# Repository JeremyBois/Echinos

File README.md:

# Echinos
Evolution of Ptechinos keyboard

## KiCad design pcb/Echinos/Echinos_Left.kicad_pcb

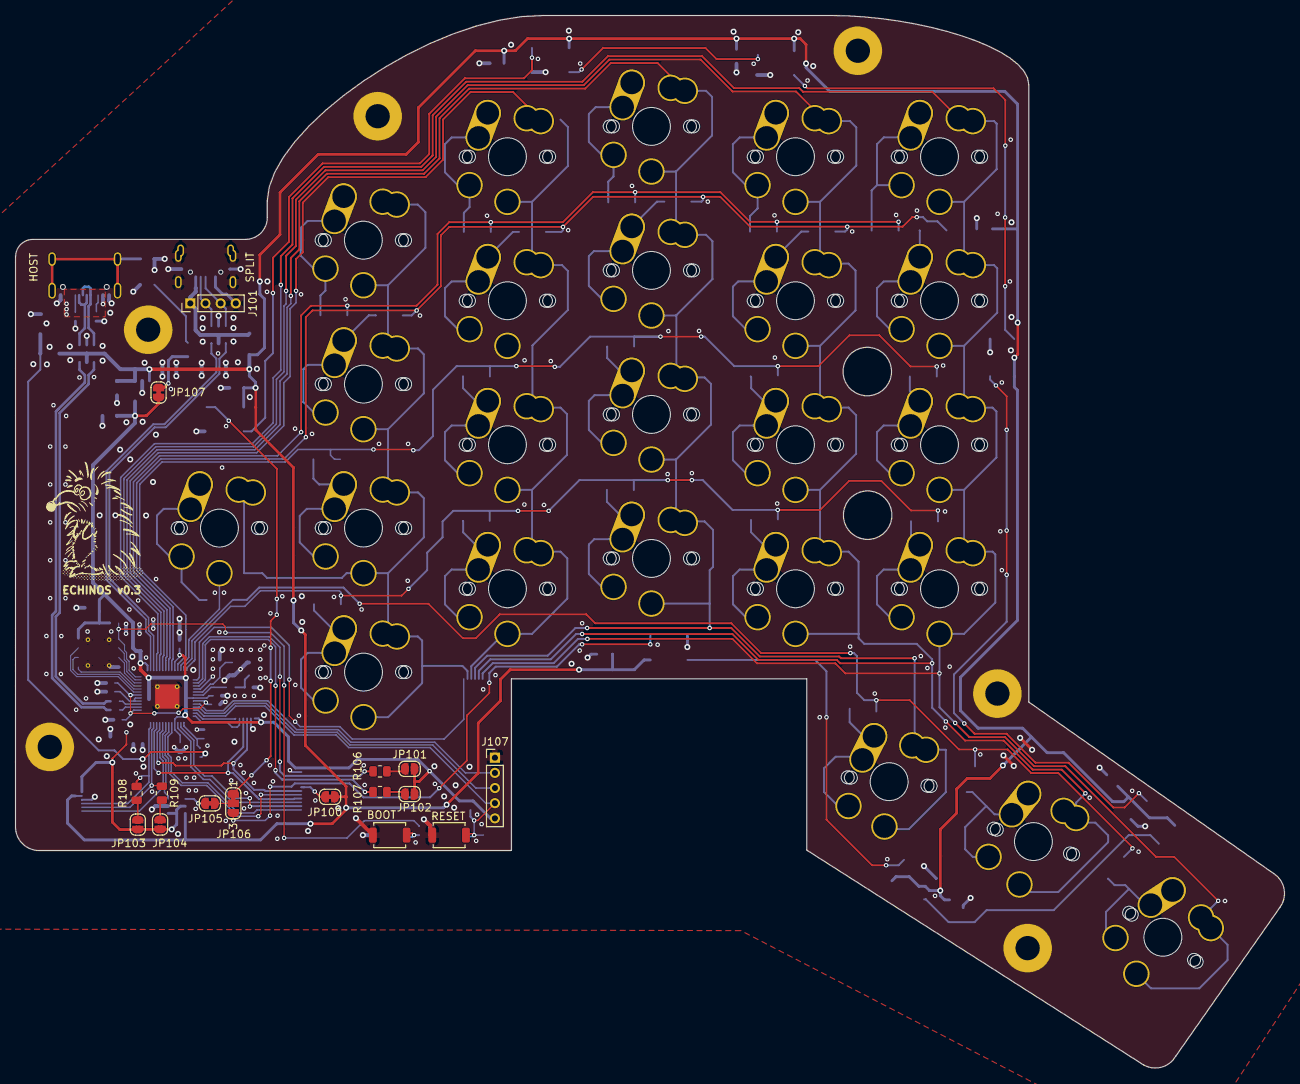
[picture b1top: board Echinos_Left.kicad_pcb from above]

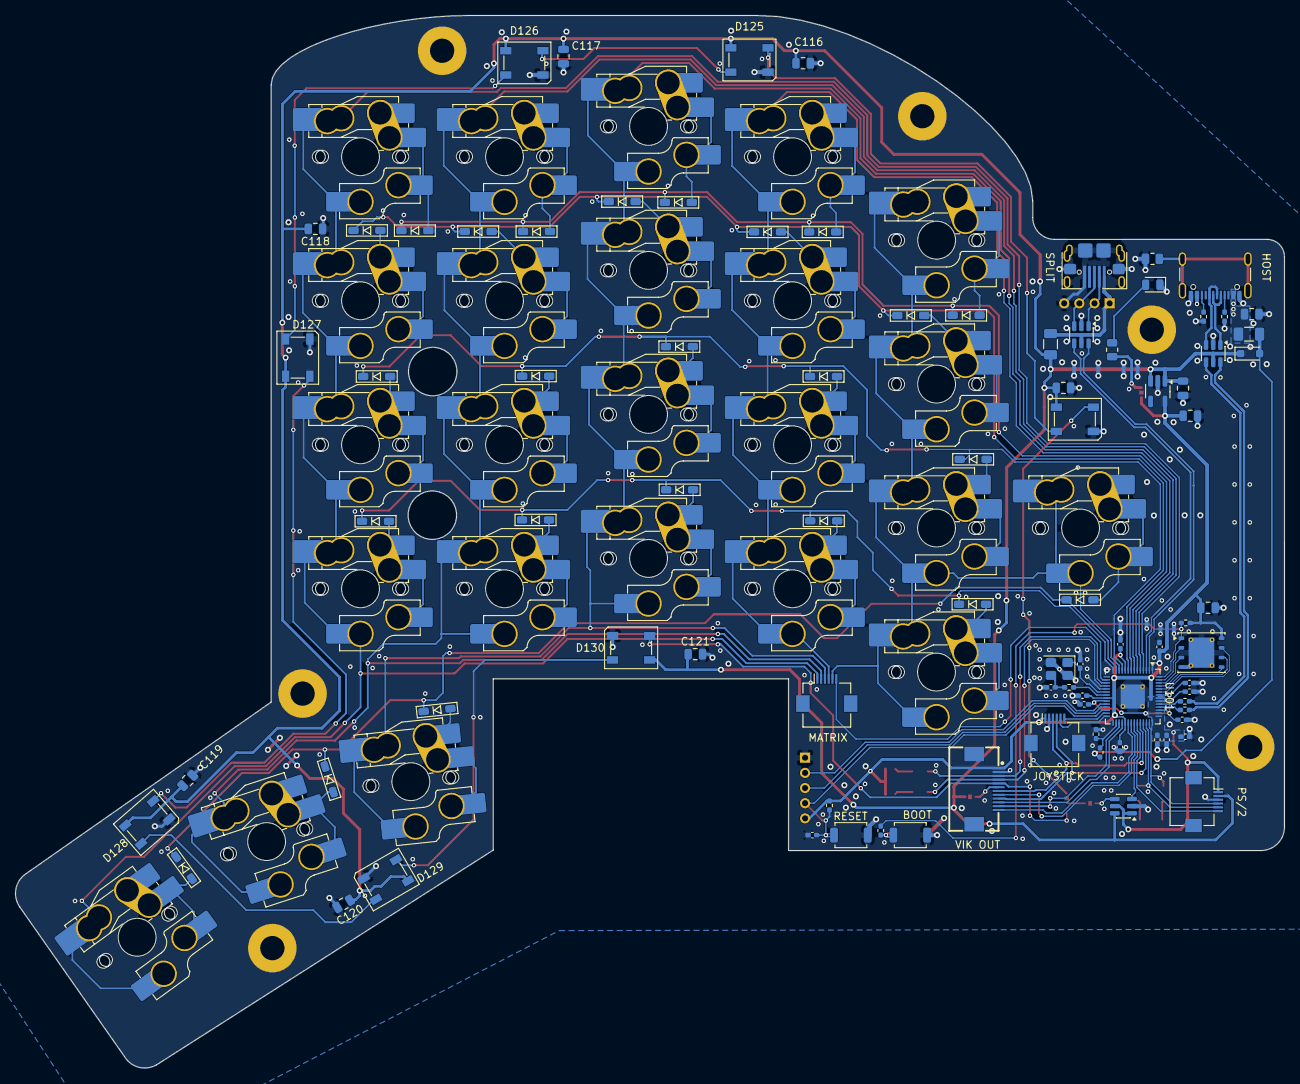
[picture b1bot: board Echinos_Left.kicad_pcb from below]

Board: 2 copper layers, 167.4 x 138.9 mm, 134 parts (87 on the bottom side), 100 nets.

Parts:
A1: Echinos Logo; Graphics_Hedgehog
C100, C106, C110: 1u; C_0402_1005Metric_Pad0.74x0.62mm_HandSolder
C101, C115, C116, C117, C118, C119, C120, C121: 100n; C_0805_2012Metric
C102, C103: 15p; C_0402_1005Metric_Pad0.74x0.62mm_HandSolder
C104, C105, C107, C108, C109, C111, C112, C113, C114: 100n; C_0402_1005Metric_Pad0.74x0.62mm_HandSolder
C122: 10u; C_0805_2012Metric
C123, C124: 1u; C_0805_2012Metric
D100, D101, D102, D103, D104, D105, D106, D107, D108, D109, D110, D111, D112, D113, D114, D115, D116, D117, D118, D119, D120, D121, D122, D123: D; D_SOD123
D124, D125, D126, D127, D128, D129, D130: SK6812; LED_SK6812_PLCC4_5.0x5.0mm_P3.2mm
D131: B5817WS; D_SOD-323_HandSoldering
D132: LED; LED_0805_2012Metric
F100, F101: 500mA; Fuse_1206_3216Metric
FB100: 600R; R_0805_2012Metric
H100, H101, H102, H103, H104, H105: M3; MountingHole_3.2mm_M3_Pad
J100: USB_B_Micro; USB_Micro-B_Amphenol_type5_micro23_Horizontal
J101: Conn_01x04_Socket; PinHeader_1x04_P2.00mm_Vertical
J102: Conn_01x12_Socket; vik-keyboard-connector-horizontal
J103, J104, J105: Conn_01x06_Socket; Hirose_FH12-6S-0.5SH_1x06-1MP_P0.50mm_Horizontal
J106: USB_C_Receptacle_USB2.0; USB_C_Receptacle_GCT_USB4105-xx-A_16P_TopMnt_Horizontal
J107: Conn_01x05_Socket; PinHeader_1x05_P2.00mm_Vertical
JP100, JP105: SolderJumper_2_Bridged; SolderJumper-2_P1.3mm_Bridged_RoundedPad1.0x1.5mm
JP101, JP102, JP103, JP104: Jumper_2_Open; SolderJumper-2_P1.3mm_Open_RoundedPad1.0x1.5mm
JP106: Jumper_3_Bridged12; SolderJumper-3_P1.3mm_Bridged12_RoundedPad1.0x1.5mm_NumberL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
JP107: 3x3_LED_jumper; SolderJumper-2_P1.3mm_Bridged_RoundedPad1.0x1.5mm
R100, R102, R114: 10k; R_0402_1005Metric_Pad0.72x0.64mm_HandSolder
R101, R103: 1k; R_0402_1005Metric_Pad0.72x0.64mm_HandSolder
R104, R105: 27; R_0402_1005Metric_Pad0.72x0.64mm_HandSolder
R106, R107, R108, R109: 4.7k; R_0805_2012Metric
R110, R111, R113: 5.1k; R_0402_1005Metric_Pad0.72x0.64mm_HandSolder
R112: 1k; R_0805_2012Metric
SW100, SW101, SW102, SW103, SW104, SW105, SW106, SW107, SW108, SW109, SW110, SW111, SW112, SW113, SW114, SW115, SW116, SW117, SW118, SW119, SW120, SW121, SW122, SW123: SW_Push; SW_Choc_MX_KS33_1u_TH_hotswap
SW124, SW125, SW126, SW127: Button; SW_SPST_TS-1088-xR020
U100: W25Q128JVP; WSON-8-1EP_6x5mm_P1.27mm_EP3.4x4mm
U101: RP2040; QFN-56-1EP_7x7mm_P0.4mm_EP3.2x3.2mm_ThermalVias
U102, U104: USBLC6-2P6; SOT-23-6
U103: 74LVC1T45; SOT-23-6
U105: XC6210B332MR-G; SOT-23-5_HandSoldering
Y100: Crystal_GND24; Crystal_SMD_Abracon_ABM8G-4Pin_3.2x2.5mm

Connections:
+1V1: C104.1, C105.1, C106.1, U101.23 (DVDD), U101.45 (VREG_VOUT), U101.50 (DVDD)
+3.3V: C101.1, C107.1, C108.1, C109.1, C110.1, C111.1, C112.1, C113.1, C114.1, C124.1, J102.1 (3V3), J104.1, J105.1, J107.5, JP101.1 (A), JP102.1 (A), JP103.1 (A), JP104.1 (A), JP107.1 (A), R100.1, R102.2, U100.8 (VCC), U101.1 (IOVDD), U101.10 (IOVDD), U101.22 (IOVDD), U101.33 (IOVDD), U101.42 (IOVDD), U101.43 (ADC_AVDD), U101.44 (VREG_VIN), U101.48 (USB_VDD), U101.49 (IOVDD), U103.1 (VCCA), U103.5 (DIR), U105.5 (VOUT)
+5V: C115.1, C116.1, C117.1, C118.1, C119.1, C120.1, C121.1, C123.1, D124.3 (VDD), D125.3 (VDD), D126.3 (VDD), D127.3 (VDD), D128.3 (VDD), D129.3 (VDD), D130.3 (VDD), D131.1 (K), F100.1, J105.2, JP100.1 (A), U103.6 (VCCB), U104.5 (VBUS), U105.1 (VIN), U105.3 (CE)
/Left/Backlight/backlight_in: D124.2 (DIN), JP106.1 (A)
/Left/P_USB+: J106.A6 (D+), J106.B6 (D+), U104.3 (I/O2)
/Left/P_USB-: J106.A7 (D-), J106.B7 (D-), U104.1 (I/O1)
/Left/RP2040/GPIO19: R113.1, R114.2, U101.30 (GPIO19)
/Left/RP2040/QSPI_SCLK: U100.6 (CLK), U101.52 (QSPI_SCLK)
/Left/RP2040/QSPI_SD0: U100.5 (DI/IO_{0}), U101.53 (QSPI_SD0)
/Left/RP2040/QSPI_SD1: U100.2 (DO/IO_{1}), U101.55 (QSPI_SD1)
/Left/RP2040/QSPI_SD2: U100.3 (~WP/IO_{2}), U101.54 (QSPI_SD2)
/Left/RP2040/QSPI_SD3: U100.7 (~HOLD/~RESET/IO_{3}), U101.51 (QSPI_SD3)
/Left/RP2040/QSPI_SS: R101.2, R102.1, U100.1 (~CS), U101.56 (~QSPI_SS)
/Left/USB+: R104.1, U104.4 (I/O2)
/Left/USB-: R105.1, U104.6 (I/O1)
GND: C100.2, C101.2, C102.1, C103.1, C104.2, C105.2, C106.2, C107.2, C108.2, C109.2, C110.2, C111.2, C112.2, C113.2, C114.2, C115.2, C116.2, C117.2, C118.2, C119.2, C120.2, C121.2, C122.2, C123.2, C124.2, D124.1 (VSS), D125.1 (VSS), D126.1 (VSS), D127.1 (VSS), D128.1 (VSS), D129.1 (VSS), D130.1 (VSS), D132.1 (K), FB100.2, H100.1 (1_1), H101.1 (1_1), H102.1 (1_1), H103.1 (1_1), H104.1 (1_1), H105.1 (1_1), J100.5 (GND), J100.SH (Shield), J101.4, J102.2 (GND), J104.2, J105.3, J106.A1 (GND), J106.A12 (GND), J106.B1 (GND), J106.B12 (GND), J107.1, R110.2, R111.2, R114.1, SW124.1, SW125.2, SW126.1, SW127.2, U100.4 (GND), U100.9 (EP), U101.19 (TESTEN), U101.57 (GND), U102.2 (GND), U103.2 (GND), U104.2 (GND), U105.2 (GND), Y100.2 (G), Y100.4 (G)
unnamed: C103.2, R103.2, Y100.3
unnamed: D100.2 (A), SW100.2
unnamed: D101.2 (A), SW101.2
unnamed: D102.2 (A), SW102.2
unnamed: D103.2 (A), SW103.2
unnamed: D104.2 (A), SW104.2
unnamed: D105.2 (A), SW105.2
unnamed: D106.2 (A), SW106.2
unnamed: D107.2 (A), SW107.2
unnamed: D108.2 (A), SW108.2
unnamed: D109.2 (A), SW109.2
unnamed: D110.2 (A), SW110.2
unnamed: D111.2 (A), SW111.2
unnamed: D112.2 (A), SW112.2
unnamed: D113.2 (A), SW113.2
unnamed: D114.2 (A), SW118.2
unnamed: D115.2 (A), SW114.2
unnamed: D116.2 (A), SW115.2
unnamed: D117.2 (A), SW116.2
unnamed: D118.2 (A), SW117.2
unnamed: D119.2 (A), SW119.2
unnamed: D120.2 (A), SW120.2
unnamed: D121.2 (A), SW121.2
unnamed: D122.2 (A), SW122.2
unnamed: D123.2 (A), SW123.2
unnamed: D124.4 (DOUT), D125.2 (DIN)
unnamed: D125.4 (DOUT), D126.2 (DIN)
unnamed: D126.4 (DOUT), D127.2 (DIN)
unnamed: D127.4 (DOUT), D128.2 (DIN)
unnamed: D128.4 (DOUT), D129.2 (DIN)
unnamed: D129.4 (DOUT), D130.2 (DIN)
unnamed: D132.2 (A), R112.1
unnamed: J102.6 (5V), JP100.2 (B)
unnamed: J106.A5 (CC1), R111.1
unnamed: J106.B5 (CC2), R110.1
unnamed: FB100.1, J106.SH (SHIELD)
unnamed: JP101.2 (B), R106.2
unnamed: JP102.2 (B), R107.2
unnamed: JP103.2 (B), R108.2
unnamed: JP104.2 (B), R109.2
unnamed: JP105.2 (B), JP106.2 (C)
unnamed: JP107.2 (B), R112.2
unnamed: R101.1, SW124.2, SW125.1
unnamed: R105.2, U101.46 (USB_DM)
unnamed: R104.2, U101.47 (USB_DP)
unnamed: C102.2, U101.20 (XIN), Y100.1
unnamed: R103.1, U101.21 (XOUT)
P_RX: J100.3 (D+), J101.3, U102.3 (I/O2)
P_TX: J100.2 (D-), J101.2, U102.1 (I/O1)
RX: U101.3 (GPIO1), U102.4 (I/O2)
TX: U101.2 (GPIO0), U102.6 (I/O1)
VBUS: D131.2 (A), F101.2, R113.2
VBUS_RAW: C122.1, F101.1, J106.A4 (VBUS), J106.A9 (VBUS), J106.B4 (VBUS), J106.B9 (VBUS)
VBUS_split: F100.2, J100.1 (VBUS), J101.1, U102.5 (VBUS)
adc_0: J102.7 (GP_AD1), J104.3, U101.38 (GPIO26/ADC0)
adc_1: J102.9 (GP_AD2), J104.4, U101.39 (GPIO27/ADC1)
col1: J103.5, SW100.1, SW101.1, SW102.1, SW103.1, SW104.1, U101.12 (GPIO9)
col2: J103.4, SW105.1, SW106.1, SW107.1, SW108.1, U101.7 (GPIO5)
col3: J103.3, SW109.1, SW110.1, SW111.1, SW112.1, SW113.1, U101.6 (GPIO4)
col4: J103.2, SW114.1, SW115.1, SW116.1, SW117.1, SW118.1, U101.5 (GPIO3)
col5: J103.1, SW119.1, SW120.1, SW121.1, SW122.1, SW123.1, U101.4 (GPIO2)
col6: J104.6, U101.27 (GPIO16)
csn1: J102.10 (SPI_CS), U101.32 (GPIO21)
miso1: J102.11 (MISO), U101.31 (GPIO20)
mosi1: J102.8 (MOSI), U101.35 (GPIO23)
ps2_clk: J105.5, R109.1, U101.40 (GPIO28/ADC2)
ps2_data: J105.4, R108.1, U101.41 (GPIO29/ADC3)
ps2_reset: J105.6, U101.37 (GPIO25)
reset: C100.1, J107.4, R100.2, SW126.2, SW127.1, U101.26 (RUN)
rgb: U101.36 (GPIO24), U103.3 (A)
rgb_5V: JP105.1 (A), U103.4 (B)
rgb_out: D130.4 (DOUT), J102.5 (RGB_DO), JP106.3 (B)
row1: D104.1 (K), D113.1 (K), D114.1 (K), D123.1 (K), U101.13 (GPIO10)
row2: D103.1 (K), D108.1 (K), D112.1 (K), D118.1 (K), D122.1 (K), U101.14 (GPIO11)
row3: D102.1 (K), D107.1 (K), D111.1 (K), D117.1 (K), D121.1 (K), U101.11 (GPIO8)
row4: D101.1 (K), D106.1 (K), D110.1 (K), D116.1 (K), D120.1 (K), U101.9 (GPIO7)
row5: D100.1 (K), D105.1 (K), D109.1 (K), D115.1 (K), D119.1 (K), U101.8 (GPIO6)
row6: J103.6, U101.16 (GPIO13)
row7: J104.5, U101.28 (GPIO17)
sck1: J102.12 (SCLK), U101.34 (GPIO22)
scl1: J102.4 (SCL), R107.1, U101.18 (GPIO15)
sda1: J102.3 (SDA), R106.1, U101.17 (GPIO14)
swclk: J107.2, U101.24 (SWCLK)
swdio: J107.3, U101.25 (SWDIO)

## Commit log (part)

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2023-04-18 🎉 [Case] - Add prototype of keyboard 3D case / tester.
2023-04-19 ⚗️ [Case] - Add Ptechinos PCB shape and adjust thumb cluster accordingly.
2023-04-25 🔧 [Git] - Add `.gitattributes`.
2023-04-29 ♻️ [Case] - Update code base according to file / variable / module refactoring.
2023-04-29 ✨ ♻️ [Case] - Replace bottom plate with 3D shell with support for both PCB and top plate. Adjust thumb layout based on Ptechinos spacing and angle.
2023-04-29 ✨ [Case] - Add modules to apply common 2D CAD transform (fillet, round, ...).
2023-04-29 ✨ [Case] - Module to add 3D rounding during linear extrusion.
2023-04-29 ♻️ [Case] - Move dict like to proper file. Add more misc operators.
2023-04-30 🩹 ♻️ [Case] - Take advantage of hull to compute footprint for reversible encoder. Fix horizontal holes position.
2023-05-01 ✨ ♻️ [Case] - Add dict function to retrieve the key from the data.
2023-05-01 ✨ [Case] - Add helper functions to make easier to move between scalar / 2D and 3D vectors.
2023-05-01 ✨ [Case] - Add an enum like to control drawing of shapes (footprint, model, cutout). Better than using multiple boolean.
2023-05-12 ✨ [Case] - Add generic 3D model of pin headers for both male and female.
2023-05-12 ✨ 🍱 [Case] - Add 3D model (STL and module) of RP2040 zero MCU.
2023-05-12 ✨ ✅ [Case] - Add octagon shape and update tests accordingly.
2023-05-12 ♻️ 💄 [Case] - Add round case shell to keyboard. Adjust thumb cluster to be more like ptechinos cluster. Use better colors (Solarized) for plates and shell.
2023-05-12 ♻️ [Case] - Now using centerZ in place of center to be more explicit.
2023-05-12 ✨ [Case] - Enum like for available draw modes.
2023-05-12 ✨ ♻️ [Case] - Now using draw mode to control if we want to draw model/footprint/clearance. Improve how clearance is computed (plate height and thickness no more required). Now using explicit part nam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
2023-05-12 ✨ [Case] - Add model/footprint/clearance for TRRS female connector.
2023-05-13 ♻️ [Case] - Now using proper module to evenly space shapes in tests. Also avoid code duplication.
2023-05-13 🔥 [Case] - Remove too generic models. Now using descriptive part name.
2023-05-28 ♻️ [Case] - Add more named axis for convenience.
2023-05-28 🩹 [Case] - Spacing functions used in tests now correctly account for the step argument.
2023-05-28 ♻️ [Case] - Add more helper method to transform from/to scalar/vector.
2023-05-28 ✨ ♻️ ✅ [Case] - Use dict like structure to make generic model for header pins (male / female). Complete footprint/clearance/model and add test cases for both male and female.
2023-05-28 ✨ ♻️ [Case] - Refactor of existing components (switch, TRRS, encoder) adding centerXY option.
2023-05-28 ✨ ♻️ [Case] - Add mcu board and TRRS to keyboard. Keycaps are now hidden by default. Clean keyboard data organization.
2023-06-18 🎉 🚧 [PCB] - Board draft schematic with embedded RP2040 chip. - 12Mhz Oscillator - USB (with ESD protection) - Voltage regulator - Flash memory (16Mo) - Reset and boot buttons - Trackpad / Trackball w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
2023-06-22 🐛 [Case] - Fix position of horizontal electrical pins on roller encoder part.
2023-06-25 ✨ ♻️ 🚧 [PCB] - Continue draft schematic by adding LCSC parts / footprint assignation. Integration of trackball schematic.
2023-06-25 ♻️ [Case] - Adjust switch pin hole side accounting for previous keyboard experience.
2023-06-25 🍱 [PCB] - Add footprints - Open jumper - Pogo connector (4 pins) - Roller encoder - Tenting puck
2023-06-25 🍱 [PCB] - Add footprints for: Trackball - Diode - Switches with hotswap - RP2040
2023-07-02 ✨ [PCB] - Continue draft schematic by adding per key RGB LED.
2023-07-02 ♻️ [PCB] - Remove symbol instances linking to other projets due to copy and paste of component symbol.
2023-07-02 🔧 🙈 [Git] - Avoid versioning of temporary files.
2023-07-17 ✨ 🐛 ✅ [PCB] - Pass ERC test (exception to unconnected GPIO pins). Fix power symbol assignation to please Kicad. Fix duplicated line name (encoder / joystick) to please Kicad. Add trackball sensor con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
2023-07-17 ✨ 🍱 🔥 [PCB] - Add switch (solder / hotswap / reversible / with encoder), encoder and joystick footprints. Remove obsolete footprints.
2023-07-17 ♻️ [PCB] - Add ferrite bead between shield and ground. Assign hand solder footprints whenever possible. Complete footprint assignation.
2023-07-17 ♻️ 🔥 [PCB] - Remove duplicated symbol (RP2040) and add missing one (Mount_Tenting).
2023-11-05 ✨ 🍱 🚚 [PCB] - Add footprint for MX/ChocV1/KS33/KS27 hotswap switches + optional EC12 encoder. Move switch 3D models to proper folder. Add 3D models for KS33 and MX switches and hotswap sockets.
2023-11-05 ✨ 🚚 [PCB] - Add footprint for Pixar PMW3360 sensor. Move 3D models to proper folder.
2023-11-05 🍱 ✨ [PCB] - Add TVS diodes footprint and 3D models for both 5V (USB) and 3.3V (SATA between halves).
2023-11-05 🍱 ✨ [PCB] - Add SATA footprint and 3D model.
2023-11-05 ✨ [PCB] - Add M3 mounting hole footprint.
2023-11-05 🍱 ✨ [PCB] - Add 3D models for J-link needle / RP2040 / FPC connector.
2023-11-05 ✨ [PCB] - Complete schema and PCB for left halve. All connections are made. Optional encoder on the top outer key Optional joystick on either outer thumb or above middle thumb. Optional power LED (ju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
2023-11-06 🍱 ✨ [PCB] - Add analog joystick SKRHACE010 footprint and 3D model.
2023-11-06 🍱 ✨ [PCB] - Add 3D models for Choc / MX keycaps.
2023-11-06 ♻️ [PCB] - Use rounded rectangle (max radius ~0.25mm) instead of plain rectangle. Better manufacturability.
2023-11-06 🚧 [PCB] - Backup of a specific layout around MCU. Modules moved to a specific schematic page.
2023-11-07 ✨ [PCB] - Make some place to add a FPC connector providing a way to expand the matrix / number of keys or add a joystick and I2C pull-up resistors. Improve routing in order to minimize the number of 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
2023-11-08 🐛 [PCB] - Fix issues with footprint. Overlapping silkscreen and non closed courtyard.
2023-11-10 ✨ 🚧 [PCB] - Halves are now connected with 5.0V power to be able to expose it to modules (see VIK standard). Update the whole routing to make this happens. VBUS and 5.0V are now split with a schottky 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
2023-11-11 🍱 [PCB] - Add 3D models for WSON flash chip package.
2023-11-11 ♻️ [PCB] - Now using WSON package for flash memory chip to reduce component height. This allows FPC and memory to be closer freeing pcb space for 6 pins header.
2023-11-11 ♻️ [PCB] - Now using the same ESD protection on both SATA and USB. Add ground fill and earth fill using ferrite bead as gate between both.
2023-11-12 ♻️ [PCB] - Fill / Check LCSC part number. Still some parts without a number: - FPC connectors - SATA connector - Reset / Bootloader switches - LED
2023-11-21 🚚 [Case] - Reorganization of OpenScad project files. Split lib and tests to avoid pollution of $fn global variable. Add 2D and 3D shapes to a proper module (primitive). Move 3D models outside sources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
2023-11-21 🙈 - Temporary tests are now put inside a temp folder.
2023-11-21 ✨ [Case | PCB] - Utility that allows to get all switches positions to place them exactly in Kicad. This script use the same algorithm that OpenScad code but only print positions and angles whereas Op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
2023-11-21 ✨ 🚧 [Case] - Draft of the trackball mount based on the one used in Ptechinos keyboard.
2023-11-24 ♻️ [Case] - Replace 'TRACKBALL' with 'BALL'. $fn is now different in preview and render mode. Add more bearings holes to be used as parapet. Add small protrusion on both side of the sensor lens. Add 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
2023-11-25 💄 [PCB] - Create a smoother / cleaner cutout and improve grounding.
2023-12-23 ✨ [PCB] - Now fully compatible with Choc V2 side post.
2023-12-26 ♻️ [PCB] - Improve earth / ground connections next to USB and SATA.
2024-01-04 🚸 💥 🏗️ [PCB] - Start improving overall MCU routing to be able to make space for headers (SPI, Joystick, ...). USB + FLASH + VIK + DET + 5V --> 3.3V + ROW + COL
2024-01-04 🚸 💥 🏗️ [PCB] - Improving overall MCU routing to be able to make space for headers (SPI, Joystick, ...). SATA - DEBUG - IO(analog) - IO(spi/matrix) - OSCILLATOR -
2024-01-04 ♻️ [PCB] - Connect I2C pull-ups (optional) and power to VIK. Improve routing especially for 5.0V and VBus. Add via stitching around power lines. Add ground plane. Unsure matching length between both 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
2024-03-03 🐛 [PCB] - Fix Joystick SKRHACE010 footprint. Spacing was not taking account the correct pad size.
2024-03-03 ♻️ [PCB] - Remove spreading on the left of the index (outer columns) because it push the upper pinky key farther (it was important to make easier to reach pinky keys on the outer side of the pinky co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
2024-03-03 💥 [PCB] - Remove encoder on top pinky as this key is now used in my current layout thanks to alt fingering removing the awkward movement required to move the pinky up. Not sure i will put and encoder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
2025-04-22 ✨ [Case] - Add sandbox to test layouts. Add parametric columns or key holder. Add parametric keyboard layout. - MX_V5 is the last iteration with MX spacing without any flaws (at least none found ^^) 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
2025-12-22 ✨ [PCB] - Add SATA footprint connector.
2025-12-22 ✨ ♻ [Case] - Add thumb and columns layout version ID allowing to make it easier to identify printed prototype and corresponding data.
2026-01-01 [PCB] - Save last state with in-board MCU.
2026-01-05 [PCB] - Save last state with Gemini MCU board (with mod exposing more pins).
2026-01-25 [PCB] - Save last state with Helios MCU board and gasket tabs on PCB.
2026-01-26 [PCB] - Save last state with Helios MCU board (no gasket on PCB).
2026-03-06 [PCB] - Save last state with Helios MCU board. - Move helios PCB on the bottom side to avoid conflict while typing on the outer pinky key - Improve helios PCB (both top and bottom) with PCB edge, ori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
2026-03-06 [PCB] - Save last state with Helios MCU board. - Fix LCSC part numbers (C11, F2) - Fix pad numbering for SK6812 to match footprint and update PCB traces - Use another LCSC part for LEDs that is avail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
2026-03-07 [PCB] - Save last state with Helios MCU board and on board USB-C.
2026-03-09 [PCB] - Save last state with on board RP2040.
2026-03-25 [PCB] - Save last state with on board RP2040. - Route crystal and 1V1
2026-03-28 [PCB] - Save last state with on board RP2040. - Correct USB impedance - Improve top plane grounding - Add via at each layer switch - Fix ERC issues - Fix orientation / position of silkscreen
2026-04-03 [PCB] - Save last state with on board RP2040. - Improve routing to make easier to create mirror version - Fix courtyard for switches
2026-04-04 [PCB] - Save last state with on board RP2040. - Create right side and route all components - Component still on the bottom side to be able to merge both side for manufacturing
2026-04-04 [PCB] - Save last state with on board RP2040. - Fix flash component orientation for JLCPCB assembly - Add logo + version - Add TH in flash footprint and use the same zone fill method as for RP2040 fo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
2026-04-09 [Config] - Update .gitignore to add avoid versioning of both production, tests and new kicad history feature.
2026-04-09 [PCB] - Save last state with on board RP2040. - Move to kicad 10 - Add DRC custom rule to exclude errors on PTH for switches due to holes being too close - Move thermal via in both RP2040 and Flash m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
2026-04-12 [PCB] - Replace "PCB edge" with "PCB Edge" to be more aligned with Kicad notation.
2026-04-12 💥 [PCB] - Split schematic for left and right halves. - Required to create a common PCB to lower the manufacturing cost
2026-04-13 💥 [PCB] - Group left and right on the same PCB. - Schematics are different for each side - Split trace naming to avoid mixing right and left - Add mouse bite between both halves to make manufacturing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
2026-05-17 💄 [PCB] - Please DRC at RP2040 level with at least 2 connections on each via for thermal relief. Flip Debug connector to avoid match convention used for pin 1 (squared one) the same as for split conn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
2026-06-24 🚧 [PCB] - Adjust KS33 model height (Left)
